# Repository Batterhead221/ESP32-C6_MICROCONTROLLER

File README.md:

# ESP32-C6_MICROCONTROLLER

Custom ESP32-C6 development board with USB-C power, RGB status LED, user input, I2C expansion, OLED support, UART programming access, and onboard temperature/humidity sensing.

This board is a small ESP32-C6 bring-up and sensor demo platform. It was designed to verify core power, boot/programming flow, GPIO, RGB LED control, I2C device detection, OLED output, and live environmental sensor readings.

## Project Status

Bring-up demo verified.

The board has successfully run a combined test with:

- RGB LED control
- User button input
- I2C bus scan
- OLED output
- Live temperature/humidity readout
- UART programming through the J3 program header

## Demo Features

- ESP32-C6 microcontroller core
- USB-C power input
- 3.3V regulation
- RGB status LED
- User button
- I2C expansion header
- OLED display support
- Onboard temperature/humidity sensor
- UART programming/debug header
- Reset and boot control for bring-up

## System Role

```text
USB-C / bench power
        ↓
ESP32-C6_MICROCONTROLLER
        ↓ I2C
OLED display + temp/humidity sensor
        ↓
bring-up demo / serial debug output
```

## Key Specs

| Item | Value |
|---|---|
| MCU | ESP32-C6 |
| Main rail | +3.3V |
| Power input | USB-C |
| Programming path verified | UART through J3 program header |
| Display interface | I2C OLED |
| Sensor interface | I2C temp/humidity sensor |
| OLED address | `0x3C` |
| Temp/humidity sensor address | `0x44` |
| RGB LED behavior | Active-low |
| Board role | ESP32-C6 bring-up/demo board |

## Verified Working

- USB-C power input
- 3.3V regulation
- ESP32-C6 boot from flash
- UART programming through J3
- Reset button
- Boot button/manual boot sequence
- User button
- RGB LED
- I2C bus
- OLED display at `0x3C`
- Temperature/humidity sensor at `0x44`

## Verified GPIO Map

| GPIO | Function |
|---:|---|
| GPIO3 | RGB red |
| GPIO4 | RGB green |
| GPIO5 | RGB blue |
| GPIO23 | User switch |
| GPIO6 | I2C SDA |
| GPIO7 | I2C SCL |

## RGB LED Notes

The RGB LED is active-low.

```text
GPIO LOW  → LED color ON
GPIO HIGH → LED color OFF
```

Firmware should invert the LED logic when controlling the status LED.

## I2C Devices

The following I2C devices were detected during bring-up:

| Address | Device |
|---:|---|
| `0x3C` | OLED display |
| `0x44` | Temperature/humidity sensor |

## Sample Verified Sensor Reading

Example live reading from bring-up:

```text
Temperature: 29.2 C
Humidity:    35.0 %RH
```

## UART Programming Notes

UART programming through the **J3 program header** is working.

Working connections:

| USB-UART adapter | ESP32-C6 board |
|---|---|
| TX | ESP_RXD |
| RX | ESP_TXD |
| GND | GND |

## Manual Upload Sequence

Current working upload sequence:

1. Hold **BOOT**.
2. Start upload.
3. Tap **RESET** when the tool begins connecting.
4. Release **BOOT** after connection.
5. Press **RESET** after upload to run the application.

## Native USB Status

Native USB enumeration still needs separate debug and validation.

Current programming flow uses UART through the J3 program header.

## Bring-Up Checklist

1. Inspect USB-C and regulator soldering.
2. Power from USB-C and confirm +3.3V.
3. Connect USB-UART adapter to J3.
4. Use the manual BOOT/RESET upload sequence.
5. Verify boot from flash.
6. Run I2C scanner.
7. Confirm OLED at `0x3C`.
8. Confirm temp/humidity sensor at `0x44`.
9. Verify RGB LED channels.
10. Verify user button input.
11. Run combined OLED + sensor + LED demo.

## Open Items

- Validate native USB enumeration.
- Improve programming flow beyond manual UART boot sequence.
- Add screenshots/photos of OLED and sensor demo.
- Add firmware example to the repository.

## Repository Output Images

Expected image paths for GitHub README rendering:

```text
Outputs/
  IMG/
    3D-T.png
    3D-B.png
    SCHEMATIC.png
    L1-SIG.png
    L2-GND.png
```

## Safety / Design Note

ESP32-C6_MICROCONTROLLER is a low-voltage development board. Verify regulator output, USB wiring, and UART adapter voltage level before connecting external hardware.

Designed & engineered by Brandon Shelly.

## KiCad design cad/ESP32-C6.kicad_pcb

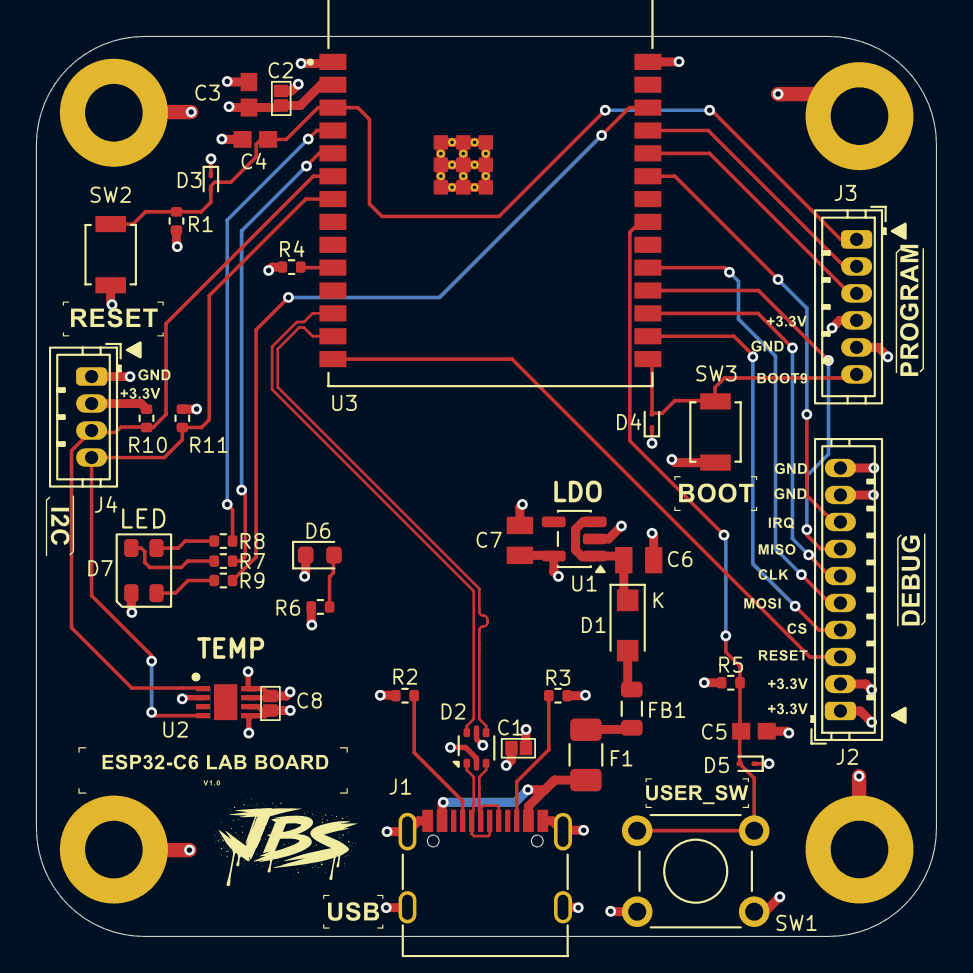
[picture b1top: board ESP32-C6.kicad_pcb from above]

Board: 4 copper layers, 50.0 x 50.0 mm, 42 parts (0 on the bottom side), 33 nets.

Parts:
C1, C2, C8: 100N; CAP 0402
C3, C4, C5: 1U; CAP 0603
C6, C7: 1U; 1UF 0805
D1: 1N5817; Nexperia_CFP3_SOD-123W
D2: USBLC6-2P6; SOT-666
D3, D4, D5: ESD9B3.3; D_SOD-923
D6: GREEN; LED_0603_1608Metric
D7: RBG_LED; LED_Cree-PLCC4_3.2x2.8mm_CCW
F1: 1A; Fuse_1206_3216Metric
FB1: 22; L_0805_2012Metric
H1, H2, H3, H4: M3; MountingHole_3.2mm_Pad
J1: USB_C; USB_C_Receptacle_G-Switch_GT-USB-7010ASV
J2: SWD; JST_ZH_B10B-ZR_1x10_P1.50mm_Vertical
J3: PROGRAM; JST_ZH_B6B-ZR_1x06_P1.50mm_Vertical
J4: S2C; JST_ZH_B4B-ZR_1x04_P1.50mm_Vertical
R1, R4, R5: 10K; R_0402_1005Metric
R2, R3: 5K1; R_0402_1005Metric
R6, R7, R8, R9: 1K; R_0402_1005Metric
R10, R11: 2K2; R_0402_1005Metric
SW1: SW_DPST; SW_TH_Tactile_Omron_B3F-100x
SW2: RESET; SW_SPST_B3U-1000P
SW3: SW_SPST_B3U-1000P
U1: LDO; SOT-23-5
U2: HDC3020DEFR; SON50P250X250X80-9N-D
U3: ESP32-C6-WROOM-1-N8; XCVR_ESP32-C6-WROOM-1-N8

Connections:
+3.3V: C1.1, C2.1, C3.1, C7.1, C8.1, D2.5 (Vbus), D7.1 (A), J2.1, J2.2, J3.4, J4.2, R1.1, R4.1, R5.1, R6.2, R10.1, R11.1, U1.5 (VOUT), U2.5 (VDD), U2.6 (~RESET), U3.2 (3V3)
+5V: C6.1, D1.1 (K), U1.1 (VIN), U1.3 (EN)
/BOOT9: D4.2 (A2), J3.6, SW3.2 (B), U3.15 (IO9)
/B_LED: R7.2, U3.5 (IO5)
/CC1: J1.A5 (CC1), R2.1
/CC2: J1.B5 (CC2), R3.1
/CLK: J2.6, U3.17 (IO19)
/CS: J2.4, U3.16 (IO18)
/D+: D2.3 (I/O2), J1.A6 (D+), J1.B6 (D+)
/D-: D2.1 (I/O1), J1.A7 (D-), J1.B7 (D-)
/ESP_EN: C4.1, D3.2 (A2), J3.1, R1.2, SW2.2 (B), U3.3 (EN)
/ESP_RXD: J3.3, U3.24 (RXD0/GPIO17)
/ESP_TXD: J3.2, U3.25 (TXD0/GPIO16)
/G_LED: R8.2, U3.4 (IO4)
/IRQ: J2.8, U3.23 (IO15)
/MISO: J2.7, U3.18 (IO20)
/MOSI: J2.5, U3.19 (IO21)
/RESET: J2.3, U3.14 (IO13)
/R_RED: R9.2, U3.26 (IO3)
/SCL: J4.4, R11.2, U2.4 (SCL), U3.7 (IO7)
/SDA: J4.3, R10.2, U2.1 (SDA), U3.6 (IO6)
/USB_D+: D2.4 (I/O2+), U3.13 (IO12)
/USB_D-: D2.6 (I/O1+), U3.12 (IO11)
/USR_SW: C5.1, D5.2 (A2), R5.2, SW1.2 (B), U3.21 (IO23)
GND: C1.2, C2.2, C3.2, C4.2, C5.2, C6.2, C7.2, C8.2, D2.2 (GND), D3.1 (A1), D4.1 (A1), D5.1 (A1), D6.1 (K), H1.1, H2.2, H3.4, H4.3, J1.A1 (GND), J1.A12 (GND), J1.B1 (GND), J1.B12 (GND), J1.S1 (SHIELD), J2.9, J2.10, J3.5, J4.1, R2.2, R3.2, SW1.1 (A), SW2.1 (A), SW3.1 (A), U1.2 (GND), U2.2 (ADDR), U2.7 (ADDR1), U2.8 (GND), U3.1 (GND), U3.28 (GND__1), U3.29 (GND__10)
unnamed: D1.2 (A), FB1.2
unnamed: D6.2 (A), R6.1
unnamed: D7.4 (BK), R7.1
unnamed: D7.3 (GK), R8.1
unnamed: D7.2 (RK), R9.1
unnamed: F1.1, J1.A4 (VBUS), J1.A9 (VBUS), J1.B4 (VBUS), J1.B9 (VBUS)
unnamed: F1.2, FB1.1
unnamed: R4.2, U3.10 (IO8)

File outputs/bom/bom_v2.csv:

BOM_V2
BOM,,,,,,,
Id,Designator,Footprint,Quantity,Designation,Supplier and ref,LCSC,
1,J3,JST_ZH_B6B-ZR_1x06_P1.50mm_Vertical,1,PROGRAM,DNP,DNP,
2,J2,JST_ZH_B10B-ZR_1x10_P1.50mm_Vertical,1,DEBUG,DNP,DNP,
3,SW2,SW_SPST_B3U-1000P,1,RESET,B3U-1100P-B,C4364316,
4,USER_SW,SW_TH_Tactile_Omron_B3F-100x,1,SW1,DNP,DNP,
5,SW3,SW_SPST_B3U-1000P,1,BOOT,B3U-1100P-B,C4364316,
6,"C3,C5,C4",CAP 0603,3,1U,CC0603KRX7R9BB105,C559769,
7,"C2,C1,C8",CAP 0402,3,100N,CC0402KRX7R9BB104,C131394,
8,U1,SOT-23-5,1,LDO,AP2112K-3.3TRG1,C23380830,
9,J4,JST_ZH_B4B-ZR_1x04_P1.50mm_Vertical,1,I2C,DNP,DNP,
10,D1,Nexperia_CFP3_SOD-123W,1,1N5817,1N5817W,C727113,
11,"R7,R9,R8,R6",R_0402_1005Metric,4,1K,RC0402JR-071KL,C105637,
12,F1,Fuse_1206_3216Metric,1,1A,JFC1206-1100FS,C136343,
13,"R2,R3",R_0402_1005Metric,2,5K1,0402WGF5101TCE,C25905,
14,"C7,C6",1UF 0805,2,1U,CC0805KKX7R8BB105,C91186,
15,U2,SON50P250X250X80-9N-D,1,LDO,HDC3020DEFR,C7472806,
16,"R10,R11",R_0402_1005Metric,2,2K2,AC0402FR-072K2L,C144773,
17,FB1,L_0805_2012Metric,1,22 OHM FERRITE BEAD,BLM21PG220SN1D,C88993,
18,"R1,R5,R4",R_0402_1005Metric,3,10K,0402 ±1% 10K,C2889342,
19,"D4,D3,D5",D_SOD-923,3,ESD9B3.3,ESD9B3.3ST5G,C96512,
20,D7,LED_Cree-PLCC4_3.2x2.8mm_CCW,1,RGB_LED,CLV1L-FKB-CJ1N1E1BB7B3B3,,
21,D2,SOT-666,1,USBLC6-2P6,USBLC6-2P6,C15999,
22,J1,USB_C_Receptacle_G-Switch_GT-USB-7010ASV,1,USB_C,GT-USB-7010ASV,C2988369,
23,D6,LED_0603_1608Metric,1,GREEN,YLED0603G,C19273151,
24,U3,XCVR_ESP32-C6-WROOM-1-N8,1,ESP32-C6-WROOM-1-N8,ESP32-C6-WROOM-1-N8,C5366877,

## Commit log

2026-04-18 file path restructure
2026-05-03 folder restructure
2026-05-13 Revised repo
